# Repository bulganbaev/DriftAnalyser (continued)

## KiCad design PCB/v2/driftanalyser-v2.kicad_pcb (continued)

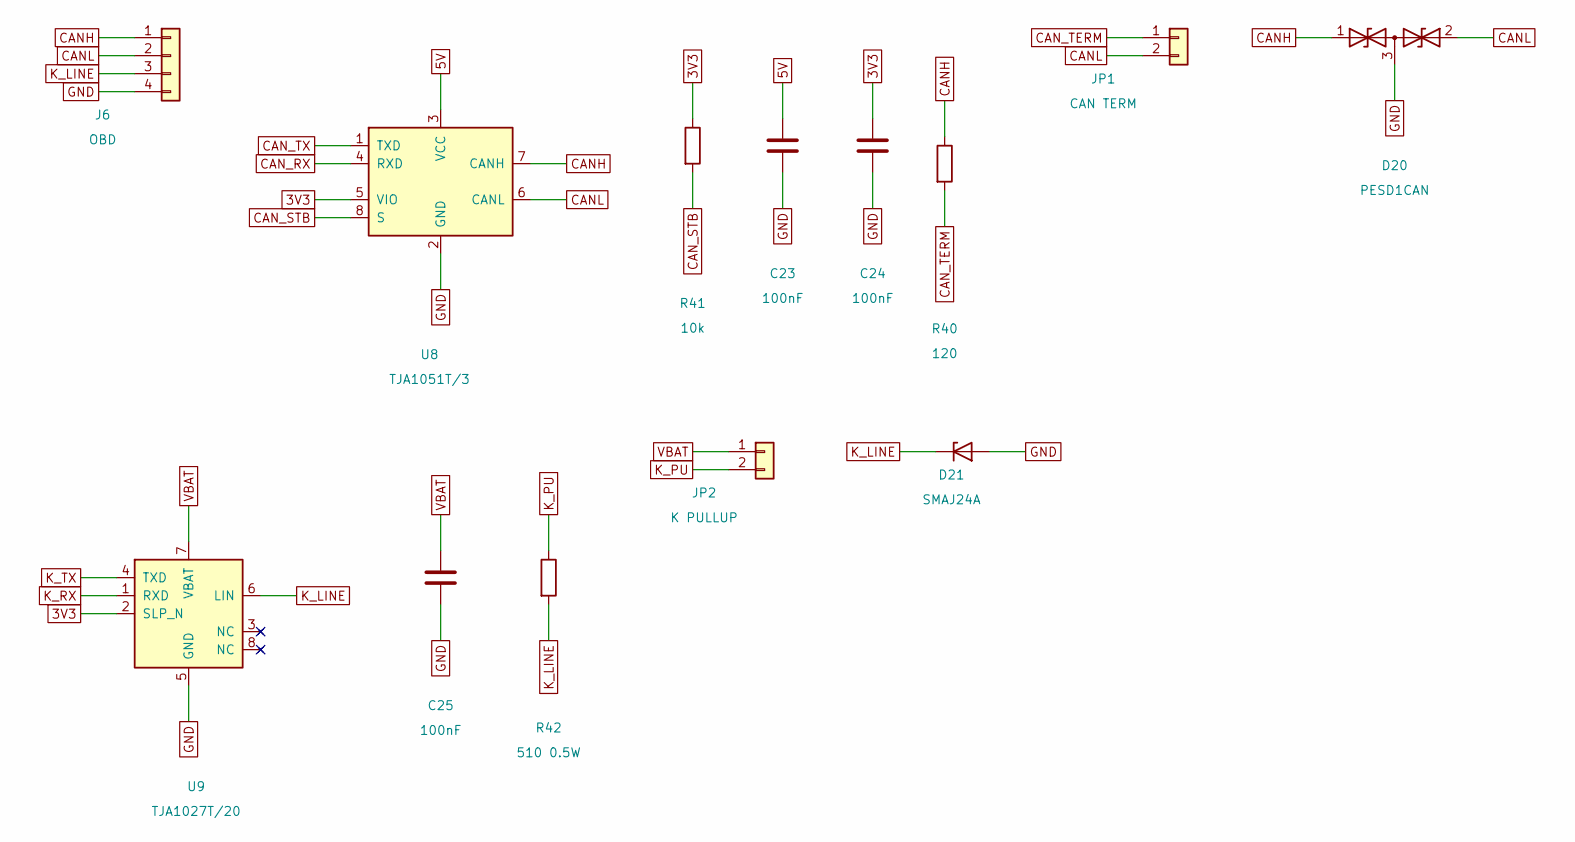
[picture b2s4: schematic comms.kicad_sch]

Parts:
C23, C24, C25: 100nF; C_0603_1608Metric; MPN CC0603KRX7R9BB104; LCSC C14663
D20: PESD1CAN; SOT-23; MPN PESD1CAN,215; LCSC C15771
D21: SMAJ24A; D_SMA; MPN SMAJ24A; LCSC C148222
J6: OBD; JST_XH_B4B-XH-A_1x04_P2.50mm_Vertical; MPN B4B-XH-A(LF)(SN); LCSC C144395
JP1: CAN TERM; PinHeader_1x02_P2.54mm_Vertical; MPN PZ254V-11-02P; LCSC C492401
JP2: K PULLUP; PinHeader_1x02_P2.54mm_Vertical; MPN PZ254V-11-02P; LCSC C492401
R40: 120; R_1206_3216Metric; MPN 1206W4F1200T5E; LCSC C17909
R41: 10k; R_0603_1608Metric; MPN 0603WAF1002T5E; LCSC C25804
R42: 510 0.5W; R_2512_6332Metric; MPN FRC2512J511TS; LCSC C2934121
U8: TJA1051T/3; SOIC-8_3.9x4.9mm_P1.27mm; MPN TJA1051T/3,118; LCSC C58988
U9: TJA1027T/20; SOIC-8_3.9x4.9mm_P1.27mm; MPN TJA1027T/20,118; LCSC C112994

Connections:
3V3: C24.1, R41.1, U8.5 (VIO), U9.2 (SLP_N); also elsewhere on the board
5V: C23.1, U8.3 (VCC); also elsewhere on the board
CANH: D20.1 (A1), J6.1, R40.1, U8.7 (CANH)
CANL: D20.2 (A2), J6.2, JP1.2, U8.6 (CANL)
CAN_RX: U8.4 (RXD); also elsewhere on the board
CAN_STB: R41.2, U8.8 (S); also elsewhere on the board
CAN_TERM: JP1.1, R40.2
CAN_TX: U8.1 (TXD); also elsewhere on the board
GND: C23.2, C24.2, C25.2, D20.3 (common), D21.2 (A), J6.4, U8.2 (GND), U9.5 (GND); also elsewhere on the board
K_LINE: D21.1 (K), J6.3, R42.2, U9.6 (LIN)
K_PU: JP2.2, R42.1
K_RX: U9.1 (RXD); also elsewhere on the board
K_TX: U9.4 (TXD); also elsewhere on the board
VBAT: C25.1, JP2.1, U9.7 (VBAT); also elsewhere on the board

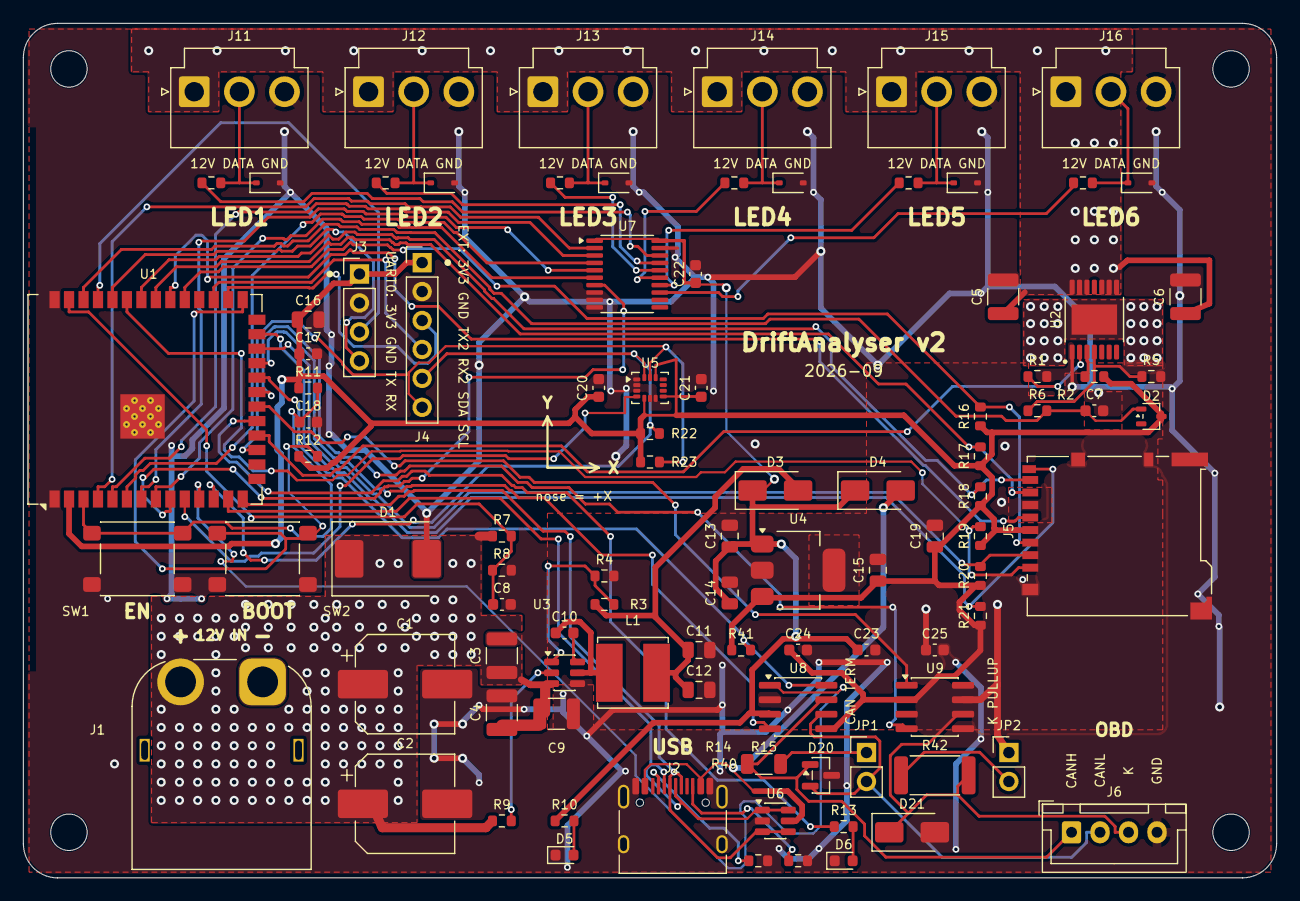
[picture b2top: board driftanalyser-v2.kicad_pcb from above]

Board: 4 copper layers, 110.0 x 75.0 mm, 101 parts (0 on the bottom side), 67 nets.

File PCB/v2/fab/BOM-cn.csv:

型号/值,位号,封装,单套数量,立创编号,厂家型号,厂家
100uF 50V,"C1,C2",CP_Elec_8x10.5,2,C2983550,GVZ1H107M0810CNVC,HRK
10uF 50V,"C3,C4,C5,C6,C9",C_1210_3225Metric,5,C2918502,CS3225X7R106K500NRL,SAMWHA
100nF,"C7,C8,C10,C17,C20,C21,C22,C23,C24,C25",C_0603_1608Metric,10,C14663,CC0603KRX7R9BB104,YAGEO
22uF 10V,"C11,C12,C13,C16",C_0805_2012Metric,4,C45783,CL21A226MAQNNNE,Samsung Electro-Mechanics
10uF,"C14,C15,C19",C_0805_2012Metric,3,C15850,CL21A106KAYNNNE,Samsung Electro-Mechanics
1uF,C18,C_0603_1608Metric,1,C15849,CL10A105KB8NNNC,Samsung Electro-Mechanics
SMDJ18A,D1,D_SMC,1,C284071,5.0SMDJ18A,DOWO
BAT54W,D2,SOT-323_SC-70,1,C77328,BAT54W,JSCJ
SS34,"D3,D4",D_SMA,2,C8678,SS34,MDD
BLUE,D5,LED_0603_1608Metric,1,C965807,XL-1608UBC-04,XINGLIGHT
GREEN,D6,LED_0603_1608Metric,1,C22371299,PSC-1608U49GC-G4,HONGLITRONIC
PESD5V0S1BA,"D11,D12,D13,D14,D15,D16",D_SOD-323,6,C19224,"PESD5V0S1BA,115",Nexperia
PESD1CAN,D20,SOT-23,1,C15771,"PESD1CAN,215",Nexperia
SMAJ24A,D21,D_SMA,1,C148222,SMAJ24A,Littelfuse
XT60PW-M,J1,AMASS_XT60PW-M_1x02_P7.20mm_Horizontal,1,C98732,XT60PW-M,AMASS
USB-C 16P,J2,USB_C_Receptacle_HRO_TYPE-C-31-M-12,1,C2765186,TYPE-C 16PIN 2MD(073),SHOU HAN
UART0,J3,PinHeader_1x04_P2.54mm_Vertical,1,C2691448,PZ254V-11-04P,XFCN
EXT,J4,PinHeader_1x06_P2.54mm_Vertical,1,C492405,PZ254V-11-06P,XFCN
microSD,J5,microSD_HC_Hirose_DM3BT-DSF-PEJS,1,C597972,DM3BT-DSF-PEJS,Hirose
OBD,J6,JST_XH_B4B-XH-A_1x04_P2.50mm_Vertical,1,C144395,B4B-XH-A(LF)(SN),JST
LED1,J11,JST_VH_B3P-VH_1x03_P3.96mm_Vertical,1,C160316,B3P-VH(LF)(SN),JST
LED2,J12,JST_VH_B3P-VH_1x03_P3.96mm_Vertical,1,C160316,B3P-VH(LF)(SN),JST
LED3,J13,JST_VH_B3P-VH_1x03_P3.96mm_Vertical,1,C160316,B3P-VH(LF)(SN),JST
LED4,J14,JST_VH_B3P-VH_1x03_P3.96mm_Vertical,1,C160316,B3P-VH(LF)(SN),JST
LED5,J15,JST_VH_B3P-VH_1x03_P3.96mm_Vertical,1,C160316,B3P-VH(LF)(SN),JST
LED6,J16,JST_VH_B3P-VH_1x03_P3.96mm_Vertical,1,C160316,B3P-VH(LF)(SN),JST
CAN TERM,JP1,PinHeader_1x02_P2.54mm_Vertical,1,C492401,PZ254V-11-02P,XFCN
K PULLUP,JP2,PinHeader_1x02_P2.54mm_Vertical,1,C492401,PZ254V-11-02P,XFCN
6.8uH,L1,L_Bourns_SRN6045TA,1,C341066,YNR6045-6R8M,YJYCOIN
10k,"R1,R2,R4,R8,R11,R12,R16,R17,R18,R19,R20,R21,R41",R_0603_1608Metric,13,C25804,0603WAF1002T5E,UNI-ROYAL
57.6k,R3,R_0603_1608Metric,1,C2933240,FRC0603F5762TS,FOJAN
470,R5,R_0603_1608Metric,1,C23179,0603WAF4700T5E,UNI-ROYAL
1k,"R6,R10,R13",R_0603_1608Metric,3,C21190,0603WAF1001T5E,UNI-ROYAL
47k,R7,R_0603_1608Metric,1,C25819,0603WAF4702T5E,UNI-ROYAL
100k,R9,R_0603_1608Metric,1,C25803,0603WAF1003T5E,UNI-ROYAL
5.1k,"R14,R15",R_0603_1608Metric,2,C23186,0603WAF5101T5E,UNI-ROYAL
4.7k,"R22,R23",R_0603_1608Metric,2,C23162,0603WAF4701T5E,UNI-ROYAL
220,"R31,R32,R33,R34,R35,R36",R_0603_1608Metric,6,C22962,0603WAF2200T5E,UNI-ROYAL
120,R40,R_1206_3216Metric,1,C17909,1206W4F1200T5E,UNI-ROYAL
510 0.5W,R42,R_2512_6332Metric,1,C2934121,FRC2512J511TS,FOJAN
EN,SW1,SW_SPST_PTS645Sx43SMTR92,1,C221880,PTS645SM43SMTR92LFS,C&K
BOOT,SW2,SW_SPST_PTS645Sx43SMTR92,1,C221880,PTS645SM43SMTR92LFS,C&K
ESP32-S3-WROOM-1-N16R2,U1,ESP32-S3-WROOM-1,1,C2913205,ESP32-S3-WROOM-1-N16R2,Espressif
BTS7002-1EPP,U2,PG-TSDSO-14,1,C2680407,BTS70021EPPXUMA1,Infineon
AP63200WU-7,U3,TSOT-23-6,1,C2071868,AP63200WU-7,Diodes Incorporated
AP7361C-33E,U4,SOT-223-3_TabPin2,1,C500795,AP7361C-33E-13,Diodes Incorporated
LSM6DS3TR-C,U5,LGA-14_3x2.5mm_P0.5mm_LayoutBorder3x4y,1,C967633,LSM6DS3TR-C,STMicroelectronics
USBLC6-2SC6,U6,SOT-23-6,1,C7519,USBLC6-2SC6,STMicroelectronics
74HCT245PW,U7,TSSOP-20_4.4x6.5mm_P0.65mm,1,C5980,"74HCT245PW,118",Nexperia
TJA1051T/3,U8,SOIC-8_3.9x4.9mm_P1.27mm,1,C58988,"TJA1051T/3,118",NXP
TJA1027T/20,U9,SOIC-8_3.9x4.9mm_P1.27mm,1,C112994,"TJA1027T/20,118",NXP

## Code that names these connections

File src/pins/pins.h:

#ifndef PINS_H
#define PINS_H

// DriftAnalyser PCB v2, see PCB/v2/README.md "Карта GPIO"
#define BOOT_BUTTON_PIN 0

#define VBAT_SENSE_PIN 1   // ADC1, divider 47k/10k
#define LED_ISENSE_PIN 2   // ADC1, BTS7002 IS into 470R

// LED strip data, through 74HCT245
#define LED_PIN_1 4
#define LED_PIN_2 5
#define LED_PIN_3 6
#define LED_PIN_4 7
#define LED_PIN_5 15
#define LED_PIN_6 16

#define LED_PWR_EN_PIN 10  // BTS7002 IN, 10k pull-down: strips are off until set
#define STATUS_LED_PIN 11  // high = on

// LSM6DS3TR-C, I2C shared with the EXT connector
#define IMU_SDA_PIN 8
#define IMU_SCL_PIN 9
#define IMU_INT1_PIN 17

// TJA1027 K-line on UART1, SLP_N tied high
#define K_RX_PIN 12
#define K_TX_PIN 13

// TJA1051, S pin has a 10k pull-up (silent) until driven low
#define CAN_RX_PIN 21
#define CAN_TX_PIN 18
#define CAN_STB_PIN 14

#endif

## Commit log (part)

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2024-09-15 init
2024-09-15 pidor
2024-09-16 ignore
2024-09-16 last
2024-09-18 working
2024-09-20 doing can
2024-09-20 can status
2024-09-21 need webserver
2024-09-24 bottom
2024-09-25 release
2024-09-26 deinit
2025-01-22 working last
